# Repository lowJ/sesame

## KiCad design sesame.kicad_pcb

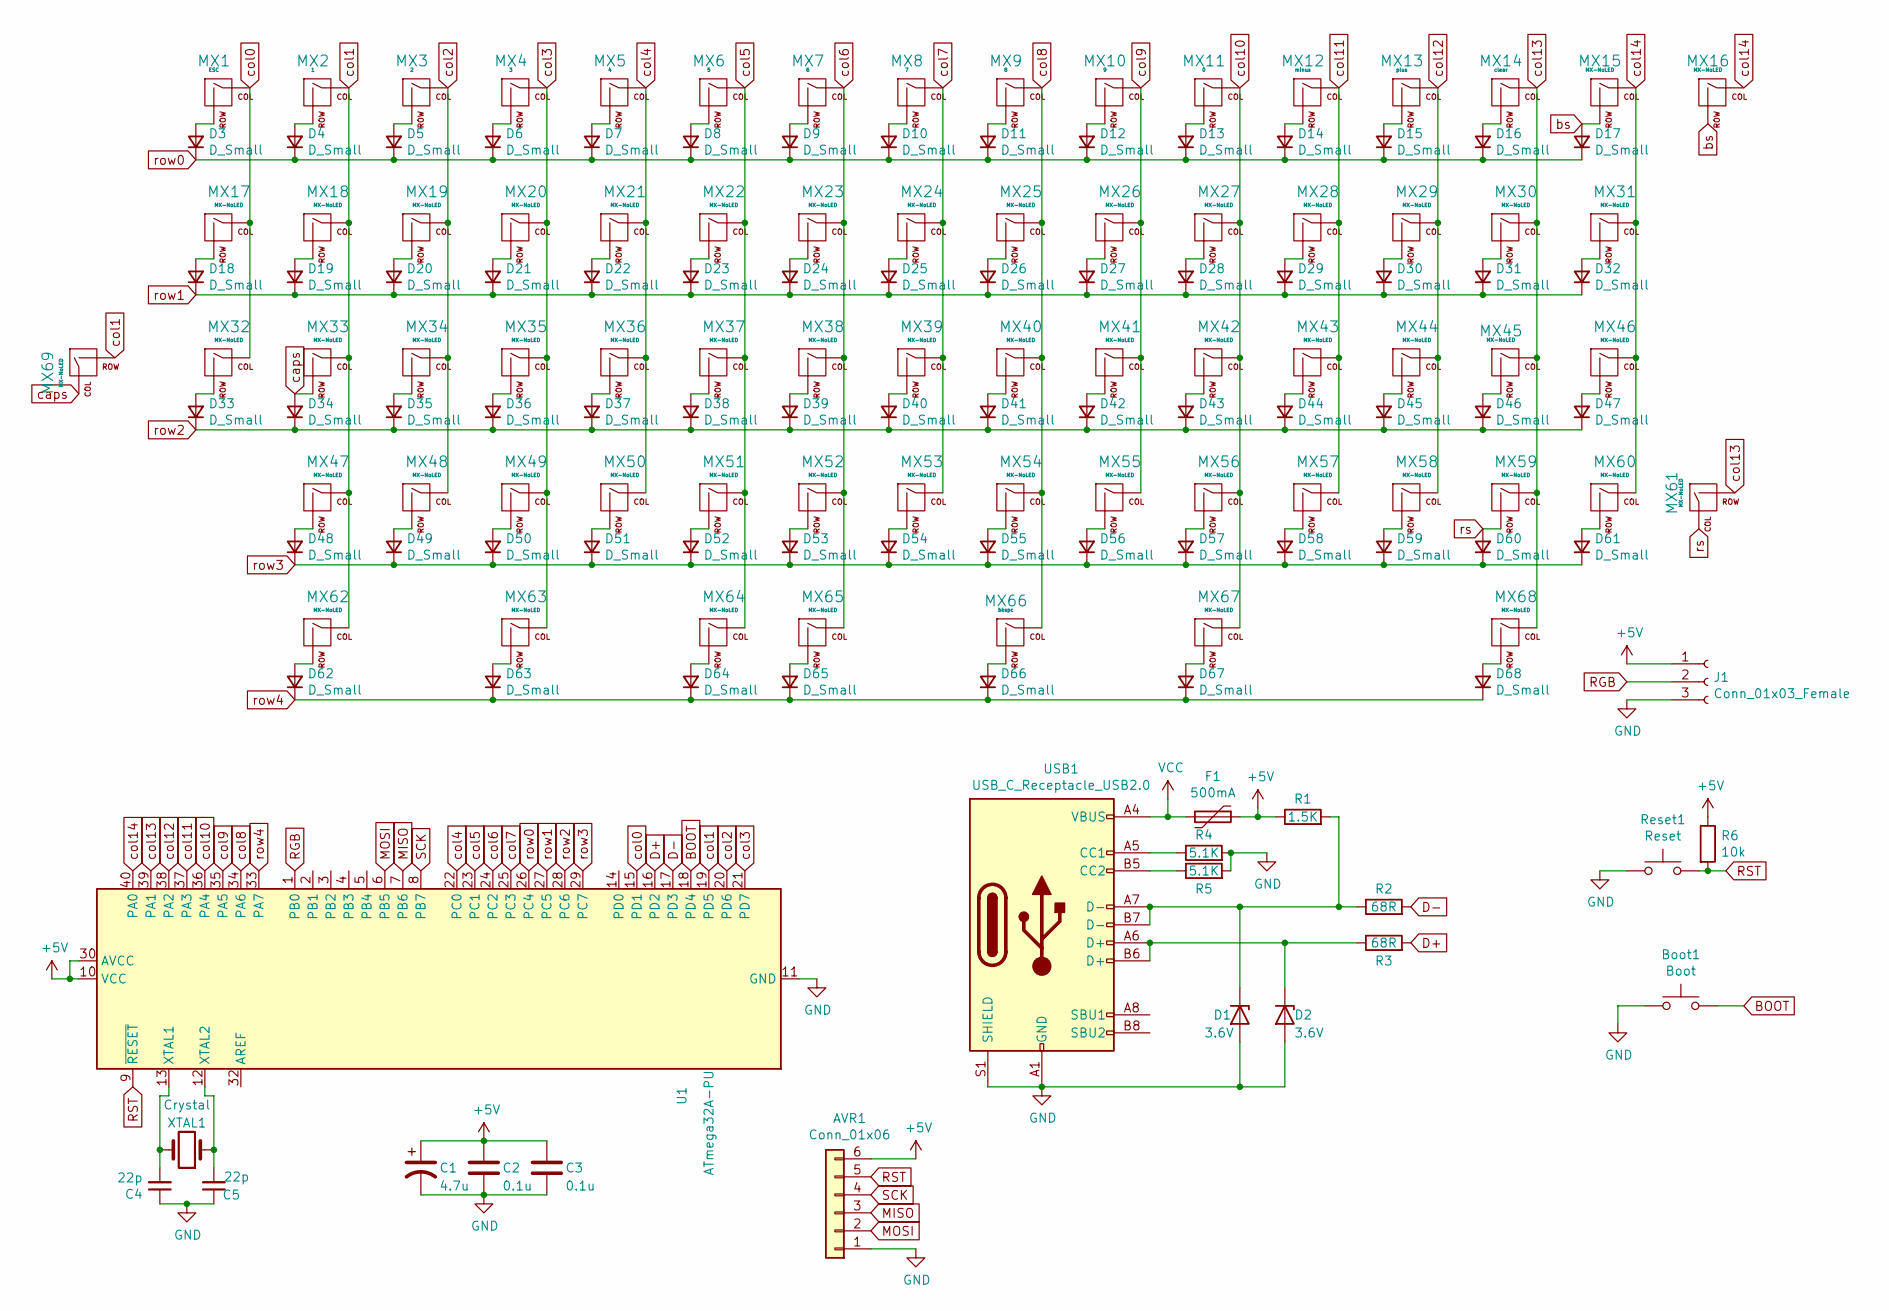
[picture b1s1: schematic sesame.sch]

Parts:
AVR1: Conn_01x06; PinHeader_1x06_P2.54mm_Vertical
Boot1: Boot; SW_PUSH_6mm
C1: 4.7u; CP_Radial_D4.0mm_P1.50mm
C2, C3: 0.1u; C_Disc_D3.0mm_W2.0mm_P2.50mm
C4, C5: 22p; C_Disc_D6.0mm_W2.5mm_P5.00mm
D1, D2: 3.6V; D_DO-35_SOD27_P7.62mm_Horizontal
D3, D4, D5, D6, D7, D8, D9, D10, D11, D12, D13, D14, D15, D16, D17, D18, D19, D20, D21, D22, D23, D24, D25, D26, D27, D28, D29, D30, D31, D32, D33, D34, D35, D36, D37, D38, D39, D40, D41, D42, D43, D44, D45, D46, D47, D48, D49, D50, D51, D52, D53, D54, D55, D56, D57, D58, D59, D60, D61, D62, D63, D64, D65, D66, D67, D68: D_Small; D_DO-35_SOD27_P7.62mm_Horizontal
F1: 500mA; Fuse_Littelfuse_395Series
J1: Conn_01x03_Female; PinHeader_1x03_P2.54mm_Vertical
MX1: ESC; MXOnly-1U-NoLED
MX2: 1; MXOnly-1U-NoLED
MX3: 2; MXOnly-1U-NoLED
MX4: 3; MXOnly-1U-NoLED
MX5: 4; MXOnly-1U-NoLED
MX6: 5; MXOnly-1U-NoLED
MX7: 6; MXOnly-1U-NoLED
MX8: 7; MXOnly-1U-NoLED
MX9: 8; MXOnly-1U-NoLED
MX10: 9; MXOnly-1U-NoLED
MX11: 0; MXOnly-1U-NoLED
MX12: minus; MXOnly-1U-NoLED
MX13: plus; MXOnly-1U-NoLED
MX14: clear; MXOnly-1U-NoLED
MX15: MX-NoLED; MXOnly-2U-NoLED
MX16, MX17, MX19, MX20, MX21, MX22, MX23, MX24, MX25, MX26, MX27, MX28, MX29, MX30, MX32, MX34, MX35, MX36, MX37, MX38, MX39, MX40, MX41, MX42, MX43, MX44, MX45, MX48, MX49, MX50, MX51, MX52, MX53, MX54, MX55, MX56, MX57, MX58, MX60, MX62, MX63, MX67, MX68: MX-NoLED; MXOnly-1U-NoLED
MX18, MX31: MX-NoLED; MXOnly-1.5U-NoLED
MX33, MX59: MX-NoLED; MXOnly-1.75U-NoLED
MX46: MX-NoLED; MXOnly-2.25U-ReversedStabilizers-NoLED
MX47: MX-NoLED; MXOnly-2.25U-NoLED
MX61: MX-NoLED; MXOnly-2.75U-NoLED
MX64: MX-NoLED; MXOnly-2U-ReversedStabilizers-NoLED
MX65, MX69: MX-NoLED; MXOnly-1.25U-NoLED
MX66: bkspc; MXOnly-2.25U-ReversedStabilizers-NoLED
R1: 1.5K; R_Axial_DIN0207_L6.3mm_D2.5mm_P10.16mm_Horizontal
R2, R3: 68R; R_Axial_DIN0207_L6.3mm_D2.5mm_P10.16mm_Horizontal
R4, R5: 5.1K; R_Axial_DIN0207_L6.3mm_D2.5mm_P10.16mm_Horizontal
R6: 10k; R_Axial_DIN0207_L6.3mm_D2.5mm_P10.16mm_Horizontal
Reset1: Reset; SW_PUSH_6mm
U1: ATmega32A-PU; DIP-40_W15.24mm
USB1: USB_C_Receptacle_USB2.0; USB_C_GCT_USB4085
XTAL1: Crystal; Crystal_HC49-4H_Vertical

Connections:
+5V: AVR1.6, C1.1, C2.1, C3.1, F1.1, J1.1, R1.1, R6.1, U1.10 (VCC), U1.30 (AVCC); also elsewhere on the board
BOOT: Boot1.2, U1.18 (PD4)
D+: R3.2, U1.16 (PD2)
D-: R2.2, U1.17 (PD3)
GND: AVR1.1, Boot1.1, C1.2, C2.2, C3.2, C4.1, C5.1, D1.2 (A), D2.2 (A), J1.3, R4.2, R5.2, Reset1.1, U1.11 (GND), U1.31 (GND), USB1.A1 (GND), USB1.A12 (GND), USB1.B1 (GND), USB1.B12 (GND), USB1.S1 (SHIELD); also elsewhere on the board
MISO: AVR1.3, U1.7 (PB6)
MOSI: AVR1.2, U1.6 (PB5)
unnamed: C4.2, U1.13 (XTAL1), XTAL1.2
unnamed: C5.2, U1.12 (XTAL2), XTAL1.1
unnamed: D1.1 (K), R1.2, R2.1, USB1.A7 (D-), USB1.B7 (D-)
unnamed: D2.1 (K), R3.1, USB1.A6 (D+), USB1.B6 (D+)
unnamed: D3.2 (A), MX1.2 (ROW)
unnamed: D4.2 (A), MX2.2 (ROW)
unnamed: D5.2 (A), MX3.2 (ROW)
unnamed: D6.2 (A), MX4.2 (ROW)
unnamed: D7.2 (A), MX5.2 (ROW)
unnamed: D8.2 (A), MX6.2 (ROW)
unnamed: D9.2 (A), MX7.2 (ROW)
unnamed: D10.2 (A), MX8.2 (ROW)
unnamed: D11.2 (A), MX9.2 (ROW)
unnamed: D12.2 (A), MX10.2 (ROW)
unnamed: D13.2 (A), MX11.2 (ROW)
unnamed: D14.2 (A), MX12.2 (ROW)
unnamed: D15.2 (A), MX13.2 (ROW)
unnamed: D16.2 (A), MX14.2 (ROW)
unnamed: D18.2 (A), MX17.2 (ROW)
unnamed: D19.2 (A), MX18.2 (ROW)
unnamed: D20.2 (A), MX19.2 (ROW)
unnamed: D21.2 (A), MX20.2 (ROW)
unnamed: D22.2 (A), MX21.2 (ROW)
unnamed: D23.2 (A), MX22.2 (ROW)
unnamed: D24.2 (A), MX23.2 (ROW)
unnamed: D25.2 (A), MX24.2 (ROW)
unnamed: D26.2 (A), MX25.2 (ROW)
unnamed: D27.2 (A), MX26.2 (ROW)
unnamed: D28.2 (A), MX27.2 (ROW)
unnamed: D29.2 (A), MX28.2 (ROW)
unnamed: D30.2 (A), MX29.2 (ROW)
unnamed: D31.2 (A), MX30.2 (ROW)
unnamed: D32.2 (A), MX31.2 (ROW)
unnamed: D33.2 (A), MX32.2 (ROW)
unnamed: D35.2 (A), MX34.2 (ROW)
unnamed: D36.2 (A), MX35.2 (ROW)
unnamed: D37.2 (A), MX36.2 (ROW)
unnamed: D38.2 (A), MX37.2 (ROW)
unnamed: D39.2 (A), MX38.2 (ROW)
unnamed: D40.2 (A), MX39.2 (ROW)
unnamed: D41.2 (A), MX40.2 (ROW)
unnamed: D42.2 (A), MX41.2 (ROW)
unnamed: D43.2 (A), MX42.2 (ROW)
unnamed: D44.2 (A), MX43.2 (ROW)
unnamed: D45.2 (A), MX44.2 (ROW)
unnamed: D46.2 (A), MX45.2 (ROW)
unnamed: D47.2 (A), MX46.2 (ROW)
unnamed: D48.2 (A), MX47.2 (ROW)
unnamed: D49.2 (A), MX48.2 (ROW)
unnamed: D50.2 (A), MX49.2 (ROW)
unnamed: D51.2 (A), MX50.2 (ROW)
unnamed: D52.2 (A), MX51.2 (ROW)
unnamed: D53.2 (A), MX52.2 (ROW)
unnamed: D54.2 (A), MX53.2 (ROW)
unnamed: D55.2 (A), MX54.2 (ROW)
unnamed: D56.2 (A), MX55.2 (ROW)
unnamed: D57.2 (A), MX56.2 (ROW)
unnamed: D58.2 (A), MX57.2 (ROW)
unnamed: D59.2 (A), MX58.2 (ROW)
unnamed: D61.2 (A), MX60.2 (ROW)
unnamed: D62.2 (A), MX62.2 (ROW)
unnamed: D63.2 (A), MX63.2 (ROW)
unnamed: D64.2 (A), MX64.2 (ROW)
unnamed: D65.2 (A), MX65.2 (ROW)
unnamed: D66.2 (A), MX66.2 (ROW)
unnamed: D67.2 (A), MX67.2 (ROW)
unnamed: D68.2 (A), MX68.2 (ROW)
unnamed: R4.1, USB1.A5 (CC1)
unnamed: R5.1, USB1.B5 (CC2)
RGB: J1.2, U1.1 (PB0); also elsewhere on the board
RST: AVR1.5, R6.2, Reset1.2, U1.9 (~RESET)
SCK: AVR1.4, U1.8 (PB7)
VCC: F1.2, USB1.A4 (VBUS), USB1.A9 (VBUS), USB1.B4 (VBUS), USB1.B9 (VBUS)
bs: D17.2 (A), MX15.2 (ROW), MX16.2 (ROW)
caps: D34.2 (A), MX33.2 (ROW), MX69.1 (COL)
col0: MX1.1 (COL), MX17.1 (COL), MX32.1 (COL), U1.15 (PD1)
col1: MX2.1 (COL), MX18.1 (COL), MX33.1 (COL), MX47.1 (COL), MX62.1 (COL), MX69.2 (ROW), U1.19 (PD5)
col2: MX3.1 (COL), MX19.1 (COL), MX34.1 (COL), MX48.1 (COL), U1.20 (PD6)
col3: MX4.1 (COL), MX20.1 (COL), MX35.1 (COL), MX49.1 (COL), MX63.1 (COL), U1.21 (PD7)
col4: MX5.1 (COL), MX21.1 (COL), MX36.1 (COL), MX50.1 (COL), U1.22 (PC0)
col5: MX6.1 (COL), MX22.1 (COL), MX37.1 (COL), MX51.1 (COL), MX64.1 (COL), U1.23 (PC1)
col6: MX7.1 (COL), MX23.1 (COL), MX38.1 (COL), MX52.1 (COL), MX65.1 (COL), U1.24 (PC2)
col7: MX8.1 (COL), MX24.1 (COL), MX39.1 (COL), MX53.1 (COL), U1.25 (PC3)
col8: MX9.1 (COL), MX25.1 (COL), MX40.1 (COL), MX54.1 (COL), MX66.1 (COL), U1.34 (PA6)
col9: MX10.1 (COL), MX26.1 (COL), MX41.1 (COL), MX55.1 (COL), U1.35 (PA5)
col10: MX11.1 (COL), MX27.1 (COL), MX42.1 (COL), MX56.1 (COL), MX67.1 (COL), U1.36 (PA4)
col11: MX12.1 (COL), MX28.1 (COL), MX43.1 (COL), MX57.1 (COL), U1.37 (PA3)
col12: MX13.1 (COL), MX29.1 (COL), MX44.1 (COL), MX58.1 (COL), U1.38 (PA2)
col13: MX14.1 (COL), MX30.1 (COL), MX45.1 (COL), MX59.1 (COL), MX61.2 (ROW), MX68.1 (COL), U1.39 (PA1)
col14: MX15.1 (COL), MX16.1 (COL), MX31.1 (COL), MX46.1 (COL), MX60.1 (COL), U1.40 (PA0)
row0: D3.1 (K), D4.1 (K), D5.1 (K), D6.1 (K), D7.1 (K), D8.1 (K), D9.1 (K), D10.1 (K), D11.1 (K), D12.1 (K), D13.1 (K), D14.1 (K), D15.1 (K), D16.1 (K), D17.1 (K), U1.26 (PC4)
row1: D18.1 (K), D19.1 (K), D20.1 (K), D21.1 (K), D22.1 (K), D23.1 (K), D24.1 (K), D25.1 (K), D26.1 (K), D27.1 (K), D28.1 (K), D29.1 (K), D30.1 (K), D31.1 (K), D32.1 (K), U1.27 (PC5)
row2: D33.1 (K), D34.1 (K), D35.1 (K), D36.1 (K), D37.1 (K), D38.1 (K), D39.1 (K), D40.1 (K), D41.1 (K), D42.1 (K), D43.1 (K), D44.1 (K), D45.1 (K), D46.1 (K), D47.1 (K), U1.28 (PC6)
row3: D48.1 (K), D49.1 (K), D50.1 (K), D51.1 (K), D52.1 (K), D53.1 (K), D54.1 (K), D55.1 (K), D56.1 (K), D57.1 (K), D58.1 (K), D59.1 (K), D60.1 (K), D61.1 (K), U1.29 (PC7)
row4: D62.1 (K), D63.1 (K), D64.1 (K), D65.1 (K), D66.1 (K), D67.1 (K), D68.1 (K), U1.33 (PA7)
rs: D60.2 (A), MX59.2 (ROW), MX61.1 (COL)

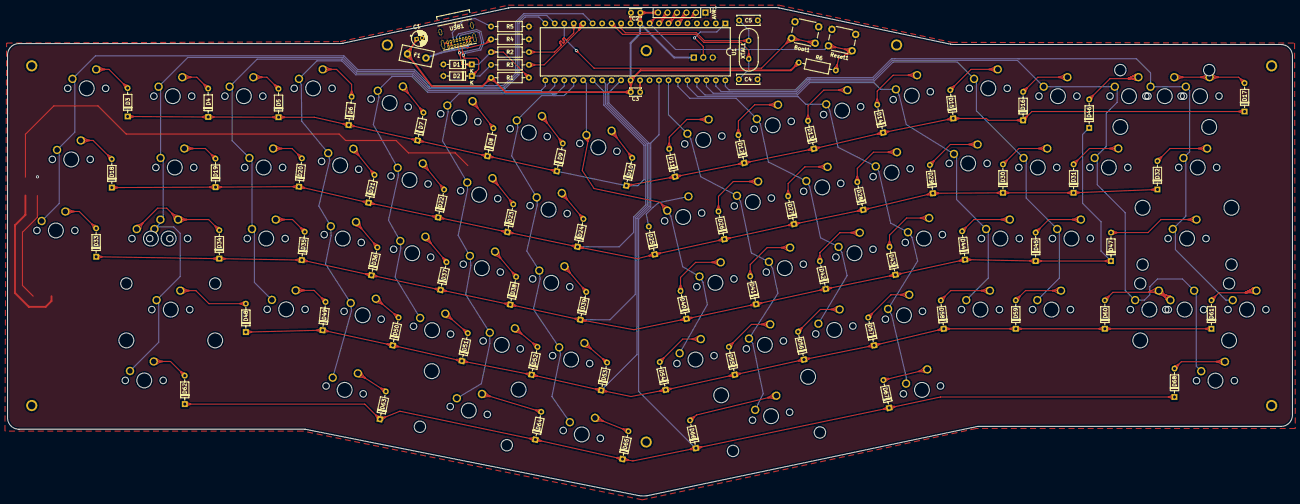
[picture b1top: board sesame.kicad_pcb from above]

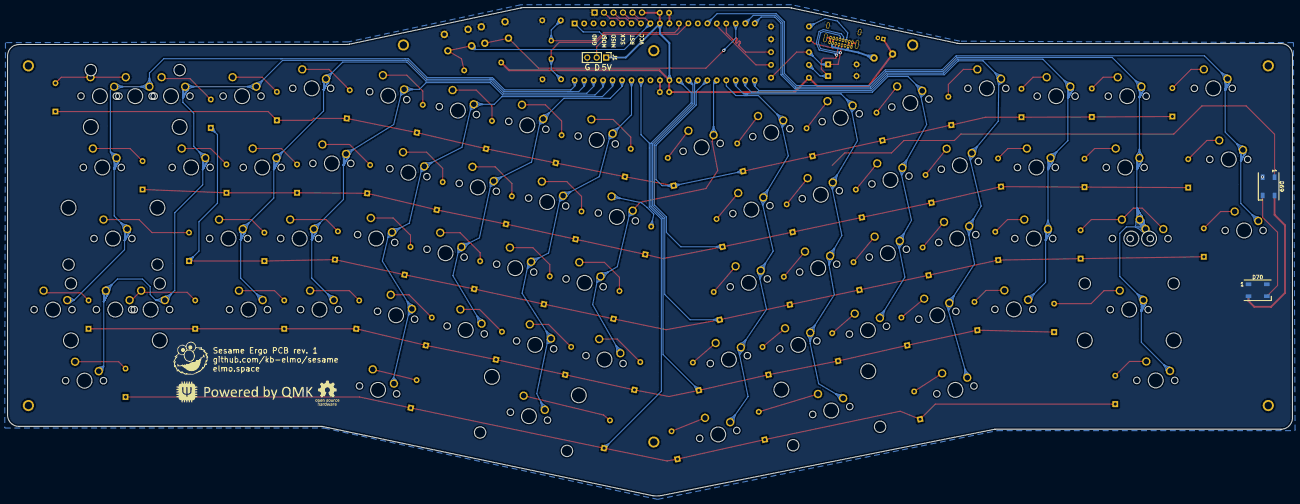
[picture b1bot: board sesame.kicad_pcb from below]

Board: 2 copper layers, 344.4 x 130.9 mm, 158 parts (3 on the bottom side), 104 nets.

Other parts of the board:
D69, D70: WS2812B; LED_WS2812B_PLCC4_5.0x5.0mm_P3.2mm

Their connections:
+5V: D69.1, D70.1; also elsewhere on the board
GND: D69.3, D70.3; also elsewhere on the board
unnamed: D69.2, D70.4
RGB: D69.4; also elsewhere on the board

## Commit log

2021-01-22 added rgb header
2021-02-14 add
    -Double check implementation of Ws2812b(ex. caps for each led), (resistor between dataline and MCU pin)
    -Add more more RGB LEDS to the schematic, generate netlist
    - OPen pcb view, read netlist, place the LEDs. Make sure on correct side. Then route traces
